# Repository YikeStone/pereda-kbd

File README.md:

# Pereda

Pereda is a custom wireless mechanical keyboard designed for **Kailh Choc V1** switches.

It has **46 keys**, aggressive **column stagger**, and **column splay**. The key positions are designed around my finger length and natural finger-joint movement rather than a conventional keyboard layout.

Finished Product:

## Hardware

* Kailh Choc V1 switches
* Seeed Studio XIAO nRF52840
* Wireless
* 46 keys
* Aggressive column stagger and column splay
* Reversible PCB
* 301230 LiPo battery, 120 mAh
* Magnetic USB-C connector for charging
* Custom ergonomic key layout

## Build Details

* **Top plate:** 1 mm laser-cut aluminum, spray-painted black
* **PCB:** Black solder mask
* **Keyboard height:** ~1.5 cm from the table surface
* **Feet:** 8 × 3 mm silicone dots to prevent sliding

## Assembly

After soldering the XIAO nRF52840 module to the PCB, a battery pad on the underside of the XIAO remains accessible through the cutout in the PCB.

Solder the exposed battery pad on the XIAO to the corresponding battery pad on the PCB using a short wire.

The PCB is reversible, allowing the same PCB design to be used for either side.

## Firmware

Pereda uses **ZMK firmware**.

[Pereda ZMK Configuration](https://github.com/YikeStone/pereda-zmk)

## Manufacturing

Ready-to-manufacture files are available under:

`manufacturing/v0.2/`

The BOM quantities are for **one PCB/half**.

## Repository

* `common/` — custom symbols, footprints, and 3D models
* `images/` — project images
* `manufacturing/` — BOM, fabrication files, DXF, and CAD
* `*.kicad_*` — KiCad source files

## Status

**v0.2 — functional prototype.**

## Acknowledgements

Inspired by the [Corne keyboard](https://github.com/foostan/crkbd) by foostan.

## License

See `LICENSE`.

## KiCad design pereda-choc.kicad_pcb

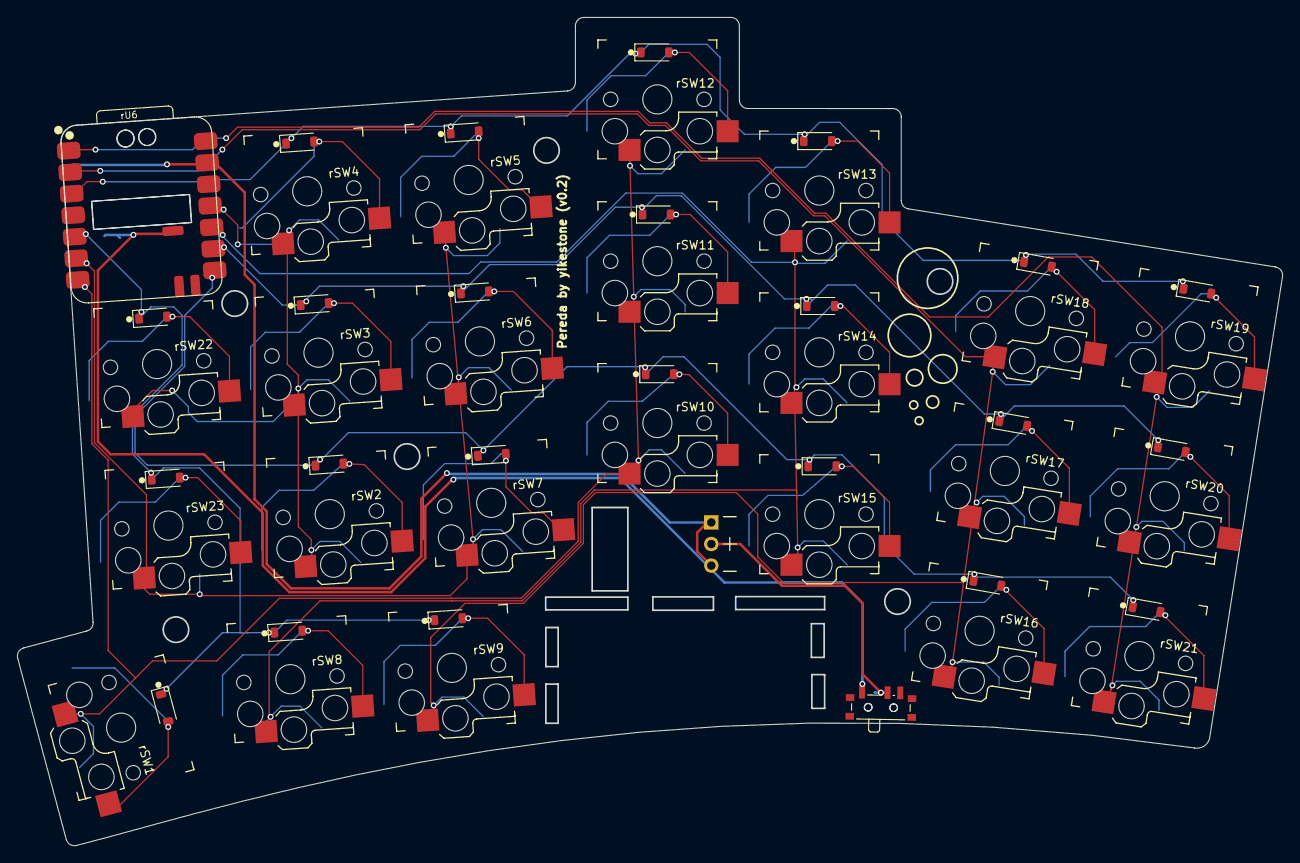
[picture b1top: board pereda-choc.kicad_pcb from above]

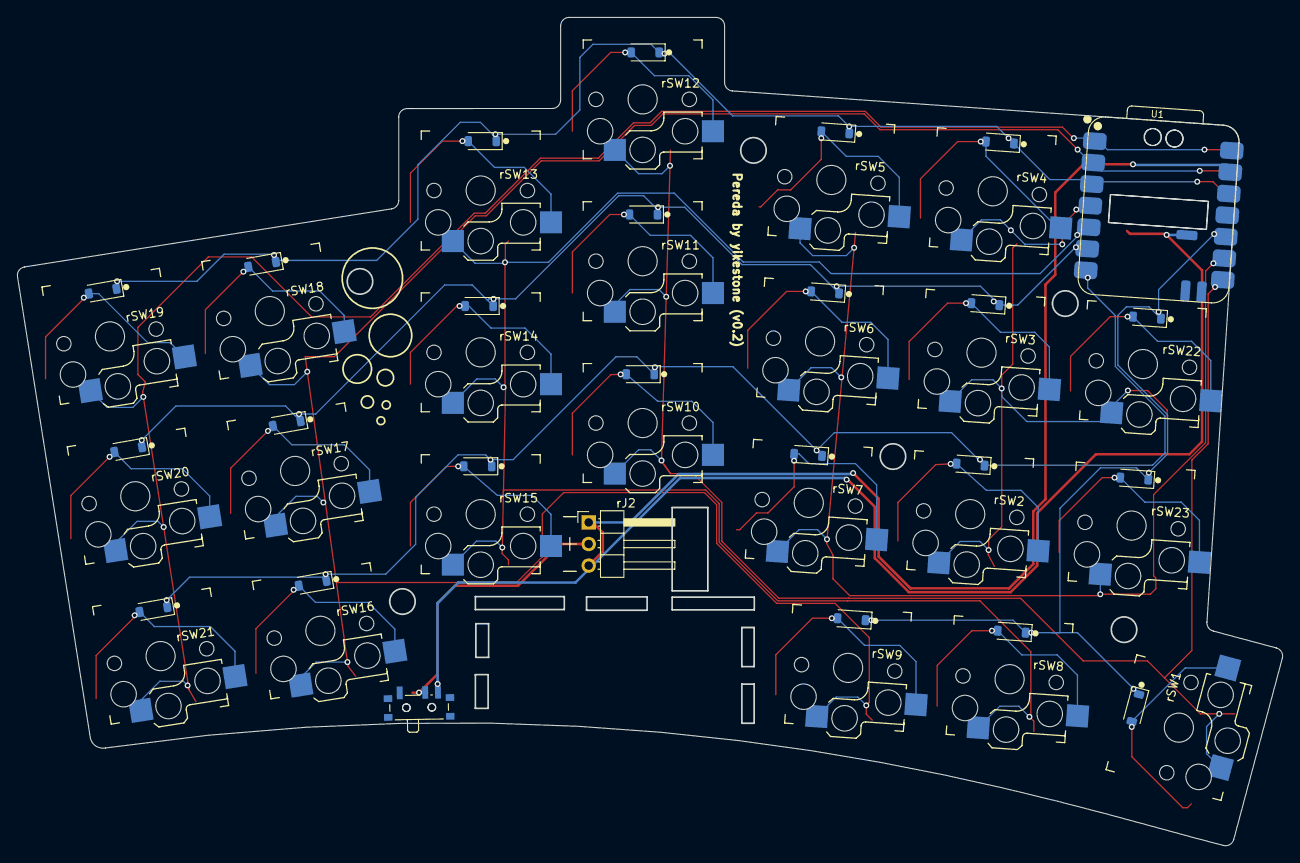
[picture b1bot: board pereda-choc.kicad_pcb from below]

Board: 2 copper layers, 148.9 x 97.5 mm, 51 parts (26 on the bottom side), 36 nets.

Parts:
D2, D3, D4, D5, D6, D7, D8, D9, D10, D11, D12, D13, D14, D15, D16, D17, D18, D19, D20, D21, D22, D23, D24: 1N4148WT; D_SOD-123-rev
SMDSW2: SPDT; SW_SPDT_PCM12
U1: XIAO-nRF52840-SMD; XIAO-nRF52840-SMD-kbd
rJ2: Conn_01x03; PinHeader_1x03_P2.54mm_Horizontal
rSMDSW1: SPDT; SW_SPDT_PCM12
rSW1: SW_Push; Kailh_socket_PG1350_reversible_1.25u
rSW2, rSW3, rSW4, rSW5, rSW6, rSW7, rSW8, rSW9, rSW10, rSW11, rSW12, rSW13, rSW14, rSW15, rSW16, rSW17, rSW18, rSW19, rSW20, rSW21, rSW22, rSW23: SW_Push; Kailh_socket_PG1350_reversible_1u
rU6: XIAO-nRF52840-SMD; XIAO-nRF52840-SMD-kbd

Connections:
COL0: U1.1 (P0.02_A0_D0), rSW19.1, rSW20.1, rSW21.1, rU6.1 (P0.02_A0_D0)
COL1: U1.2 (P0.03_A1_D1), rSW9.1, rSW16.1, rSW17.1, rSW18.1, rU6.2 (P0.03_A1_D1)
COL2: U1.5 (P0.04_A4_D4_SDA), rSW8.1, rSW13.1, rSW14.1, rSW15.1, rU6.10 (P1.14_D9_MISO)
COL3: U1.8 (P1.12_D7_RX), rSW1.1, rSW10.1, rSW11.1, rSW12.1, rU6.7 (P1.11_D6_TX)
COL4: U1.9 (P1.13_D8_SCK), rSW5.1, rSW6.1, rSW7.1, rSW23.1, rU6.6 (P0.05_A5_D5_SCL)
COL5: U1.4 (P0.29_A3_D3), rSW2.1, rSW3.1, rSW4.1, rSW22.1, rU6.11 (P1.15_D10_MOSI)
GND: U1.13 (GND), rJ2.1, rJ2.3, rU6.13 (GND)
unnamed: D2.2 (A), rSW4.2
unnamed: D3.2 (A), rSW5.2
unnamed: D4.2 (A), rSW12.2
unnamed: D5.2 (A), rSW13.2
unnamed: D6.2 (A), rSW18.2
unnamed: D7.2 (A), rSW19.2
unnamed: D8.2 (A), rSW20.2
unnamed: D9.2 (A), rSW21.2
unnamed: D10.2 (A), rSW16.2
unnamed: D11.2 (A), rSW9.2
unnamed: D12.2 (A), rSW17.2
unnamed: D13.2 (A), rSW14.2
unnamed: D14.2 (A), rSW11.2
unnamed: D15.2 (A), rSW6.2
unnamed: D16.2 (A), rSW3.2
unnamed: D17.2 (A), rSW2.2
unnamed: D18.2 (A), rSW22.2
unnamed: D19.2 (A), rSW23.2
unnamed: D20.2 (A), rSW1.2
unnamed: D21.2 (A), rSW7.2
unnamed: D22.2 (A), rSW10.2
unnamed: D23.2 (A), rSW8.2
unnamed: D24.2 (A), rSW15.2
POWER_ON: SMDSW2.2 (B), rJ2.2, rSMDSW1.2 (B)
ROW0: D2.1 (K), D3.1 (K), D4.1 (K), D5.1 (K), D6.1 (K), D7.1 (K), U1.3 (P0.28_A2_D2), rU6.3 (P0.28_A2_D2)
ROW1: D8.1 (K), D12.1 (K), D13.1 (K), D14.1 (K), D15.1 (K), D16.1 (K), U1.6 (P0.05_A5_D5_SCL), rU6.9 (P1.13_D8_SCK)
ROW2: D9.1 (K), D10.1 (K), D17.1 (K), D21.1 (K), D22.1 (K), D24.1 (K), U1.7 (P1.11_D6_TX), rU6.8 (P1.12_D7_RX)
ROW3: D11.1 (K), D18.1 (K), D19.1 (K), D20.1 (K), D23.1 (K), U1.10 (P1.14_D9_MISO), rU6.5 (P0.04_A4_D4_SDA)
VBAT: SMDSW2.1 (A), U1.19 (BAT), rSMDSW1.3 (A), rU6.19 (BAT)

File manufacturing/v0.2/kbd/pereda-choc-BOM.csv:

Reference,Qty,Value,Exclude from BOM,Exclude from Board,MPN,Manufacturer
"rSMDSW1,SMDSW2",1,SPDT,,,PCM12SMTBR,
"rSW2,rSW3,rSW4,rSW5,rSW6,rSW7,rSW8,rSW9,rSW10,rSW11,rSW12,rSW13,rSW14,rSW15,rSW16,rSW17,rSW18,rSW19,rSW20,rSW21,rSW22,rSW23",22,Kailh Choc v1,,,5118,
rSW1,1,Kailh Choc v1,,,5118,
"rU6,U1",1,XIAO-nRF52840-SMD,,,101991463,"Seeed Technology Co., Ltd"
"D2,D3,D4,D5,D6,D7,D8,D9,D10,D11,D12,D13,D14,D15,D16,D17,D18,D19,D20,D21,D22,D23,D24",23,1N4148WT,,,1N4148W,Diotec Semiconductor
